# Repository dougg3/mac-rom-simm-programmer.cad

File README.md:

# Mac ROM SIMM and Programmer PCBs

These are the CAD files for the Mac ROM SIMM and programmer project.

- 2mbsimm/ contains a FreePCB board layout file for the 2 MB ROM SIMM.
- 2mbsimm-dip/ contains Eagle schematics and board layout files for the 2 MB ROM SIMM for DIP chips.
- 8mbsimm/ contains Eagle schematics and board layout files for the 8 MB ROM SIMM.
- programmer/ contains Eagle schematics and board layout files for the SIMM programmer.

See [LICENSE.txt](https://github.com/dougg3/mac-rom-simm-programmer.cad/blob/master/LICENSE.txt) for information on the license of these PCBs. They are licensed under the [Creative Commons Attribution-NonCommercial 3.0 license](https://creativecommons.org/licenses/by-nc/3.0/legalcode). Feel free to make your own SIMMs and/or programmers for personal use, but do not sell them commercially.

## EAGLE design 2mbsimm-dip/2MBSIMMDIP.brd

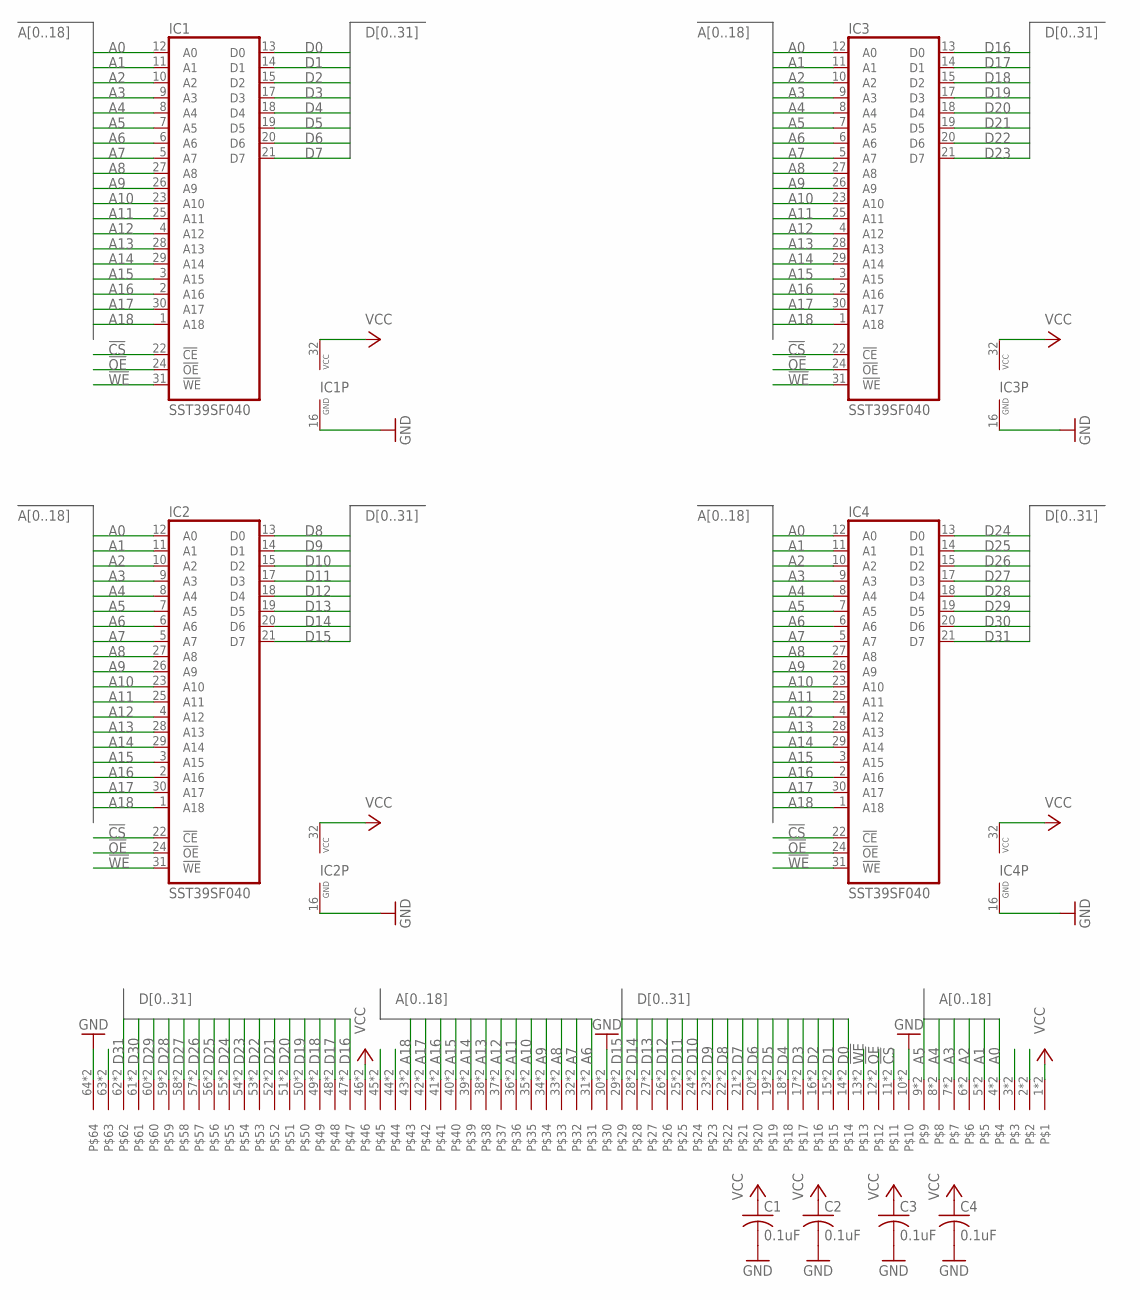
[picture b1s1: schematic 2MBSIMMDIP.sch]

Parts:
C1, C2, C3, C4: 0.1uF; C1206
CON1: MYSIMM; SIMM64L
IC1, IC2, IC3, IC4: SST39SF040; DIL32-6

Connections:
!CS: CON1.11, CON1.75, IC1.22 (!CE), IC2.22 (!CE), IC3.22 (!CE), IC4.22 (!CE)
!OE: CON1.12, CON1.76, IC1.24 (!OE), IC2.24 (!OE), IC3.24 (!OE), IC4.24 (!OE)
!WE: CON1.13, CON1.77, IC1.31 (!WE), IC2.31 (!WE), IC3.31 (!WE), IC4.31 (!WE)
A0: CON1.4, CON1.68, IC1.12 (A0), IC2.12 (A0), IC3.12 (A0), IC4.12 (A0)
A1: CON1.5, CON1.69, IC1.11 (A1), IC2.11 (A1), IC3.11 (A1), IC4.11 (A1)
A2: CON1.6, CON1.70, IC1.10 (A2), IC2.10 (A2), IC3.10 (A2), IC4.10 (A2)
A3: CON1.7, CON1.71, IC1.9 (A3), IC2.9 (A3), IC3.9 (A3), IC4.9 (A3)
A4: CON1.8, CON1.72, IC1.8 (A4), IC2.8 (A4), IC3.8 (A4), IC4.8 (A4)
A5: CON1.9, CON1.73, IC1.7 (A5), IC2.7 (A5), IC3.7 (A5), IC4.7 (A5)
A6: CON1.31, CON1.95, IC1.6 (A6), IC2.6 (A6), IC3.6 (A6), IC4.6 (A6)
A7: CON1.32, CON1.96, IC1.5 (A7), IC2.5 (A7), IC3.5 (A7), IC4.5 (A7)
A8: CON1.33, CON1.97, IC1.27 (A8), IC2.27 (A8), IC3.27 (A8), IC4.27 (A8)
A9: CON1.34, CON1.98, IC1.26 (A9), IC2.26 (A9), IC3.26 (A9), IC4.26 (A9)
A10: CON1.35, CON1.99, IC1.23 (A10), IC2.23 (A10), IC3.23 (A10), IC4.23 (A10)
A11: CON1.36, CON1.100, IC1.25 (A11), IC2.25 (A11), IC3.25 (A11), IC4.25 (A11)
A12: CON1.37, CON1.101, IC1.4 (A12), IC2.4 (A12), IC3.4 (A12), IC4.4 (A12)
A13: CON1.38, CON1.102, IC1.28 (A13), IC2.28 (A13), IC3.28 (A13), IC4.28 (A13)
A14: CON1.39, CON1.103, IC1.29 (A14), IC2.29 (A14), IC3.29 (A14), IC4.29 (A14)
A15: CON1.40, CON1.104, IC1.3 (A15), IC2.3 (A15), IC3.3 (A15), IC4.3 (A15)
A16: CON1.41, CON1.105, IC1.2 (A16), IC2.2 (A16), IC3.2 (A16), IC4.2 (A16)
A17: CON1.42, CON1.106, IC1.30 (A17), IC2.30 (A17), IC3.30 (A17), IC4.30 (A17)
A18: CON1.43, CON1.107, IC1.1 (A18), IC2.1 (A18), IC3.1 (A18), IC4.1 (A18)
D0: CON1.14, CON1.78, IC1.13 (D0)
D1: CON1.15, CON1.79, IC1.14 (D1)
D2: CON1.16, CON1.80, IC1.15 (D2)
D3: CON1.17, CON1.81, IC1.17 (D3)
D4: CON1.18, CON1.82, IC1.18 (D4)
D5: CON1.19, CON1.83, IC1.19 (D5)
D6: CON1.20, CON1.84, IC1.20 (D6)
D7: CON1.21, CON1.85, IC1.21 (D7)
D8: CON1.22, CON1.86, IC2.13 (D0)
D9: CON1.23, CON1.87, IC2.14 (D1)
D10: CON1.24, CON1.88, IC2.15 (D2)
D11: CON1.25, CON1.89, IC2.17 (D3)
D12: CON1.26, CON1.90, IC2.18 (D4)
D13: CON1.27, CON1.91, IC2.19 (D5)
D14: CON1.28, CON1.92, IC2.20 (D6)
D15: CON1.29, CON1.93, IC2.21 (D7)
D16: CON1.47, CON1.111, IC3.13 (D0)
D17: CON1.48, CON1.112, IC3.14 (D1)
D18: CON1.49, CON1.113, IC3.15 (D2)
D19: CON1.50, CON1.114, IC3.17 (D3)
D20: CON1.51, CON1.115, IC3.18 (D4)
D21: CON1.52, CON1.116, IC3.19 (D5)
D22: CON1.53, CON1.117, IC3.20 (D6)
D23: CON1.54, CON1.118, IC3.21 (D7)
D24: CON1.55, CON1.119, IC4.13 (D0)
D25: CON1.56, CON1.120, IC4.14 (D1)
D26: CON1.57, CON1.121, IC4.15 (D2)
D27: CON1.58, CON1.122, IC4.17 (D3)
D28: CON1.59, CON1.123, IC4.18 (D4)
D29: CON1.60, CON1.124, IC4.19 (D5)
D30: CON1.61, CON1.125, IC4.20 (D6)
D31: CON1.62, CON1.126, IC4.21 (D7)
GND: C1.2, C2.2, C3.2, C4.2, CON1.10, CON1.30, CON1.64, CON1.74, CON1.94, CON1.128, IC1.16 (GND), IC2.16 (GND), IC3.16 (GND), IC4.16 (GND)
UNUSED1: CON1.2, CON1.66
UNUSED2: CON1.3, CON1.67
UNUSED3: CON1.63, CON1.127
UNUSED4: CON1.44, CON1.108
UNUSED5: CON1.45, CON1.109
VCC: C1.1, C2.1, C3.1, C4.1, CON1.1, CON1.46, CON1.65, CON1.110, IC1.32 (VCC), IC2.32 (VCC), IC3.32 (VCC), IC4.32 (VCC)

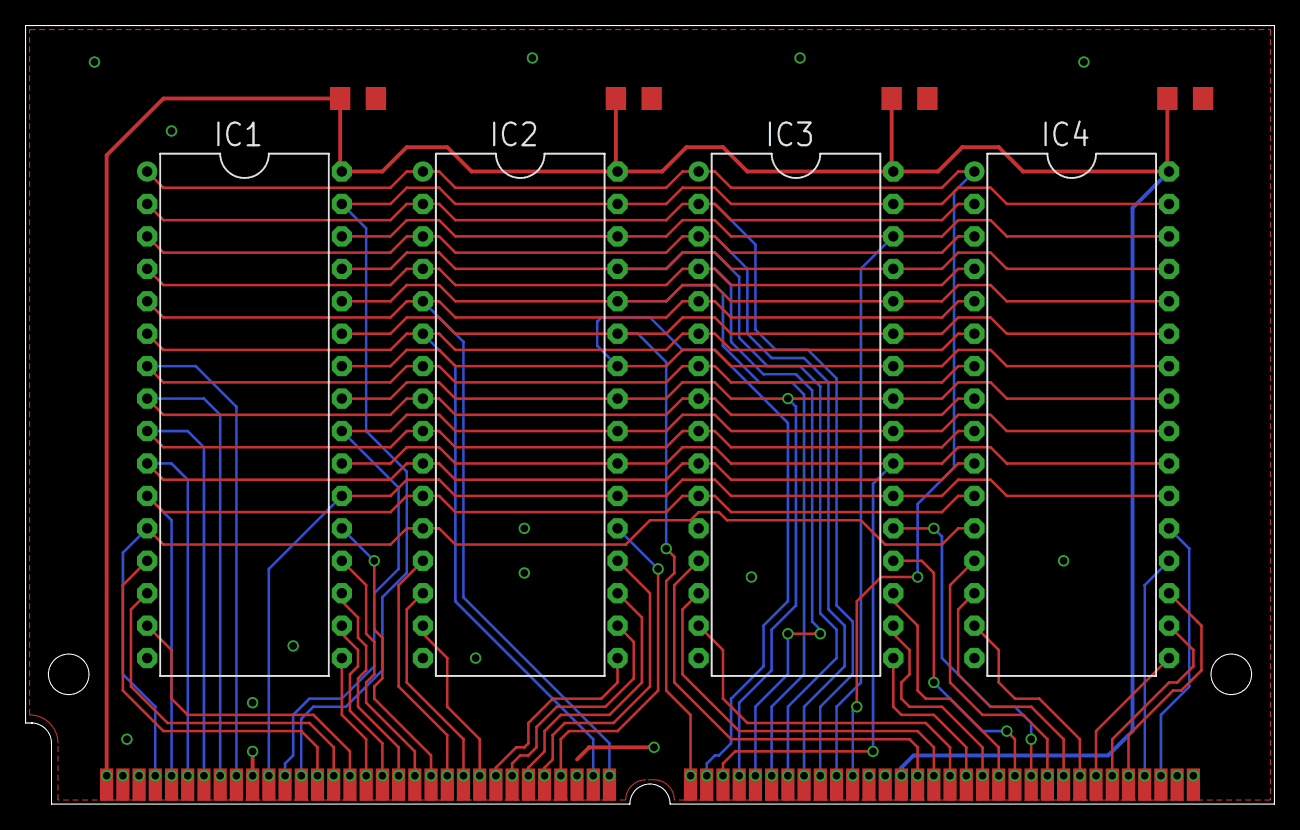
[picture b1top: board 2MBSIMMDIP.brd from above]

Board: 2 copper layers, 97.8 x 61.0 mm, 9 parts (0 on the bottom side), 61 nets.

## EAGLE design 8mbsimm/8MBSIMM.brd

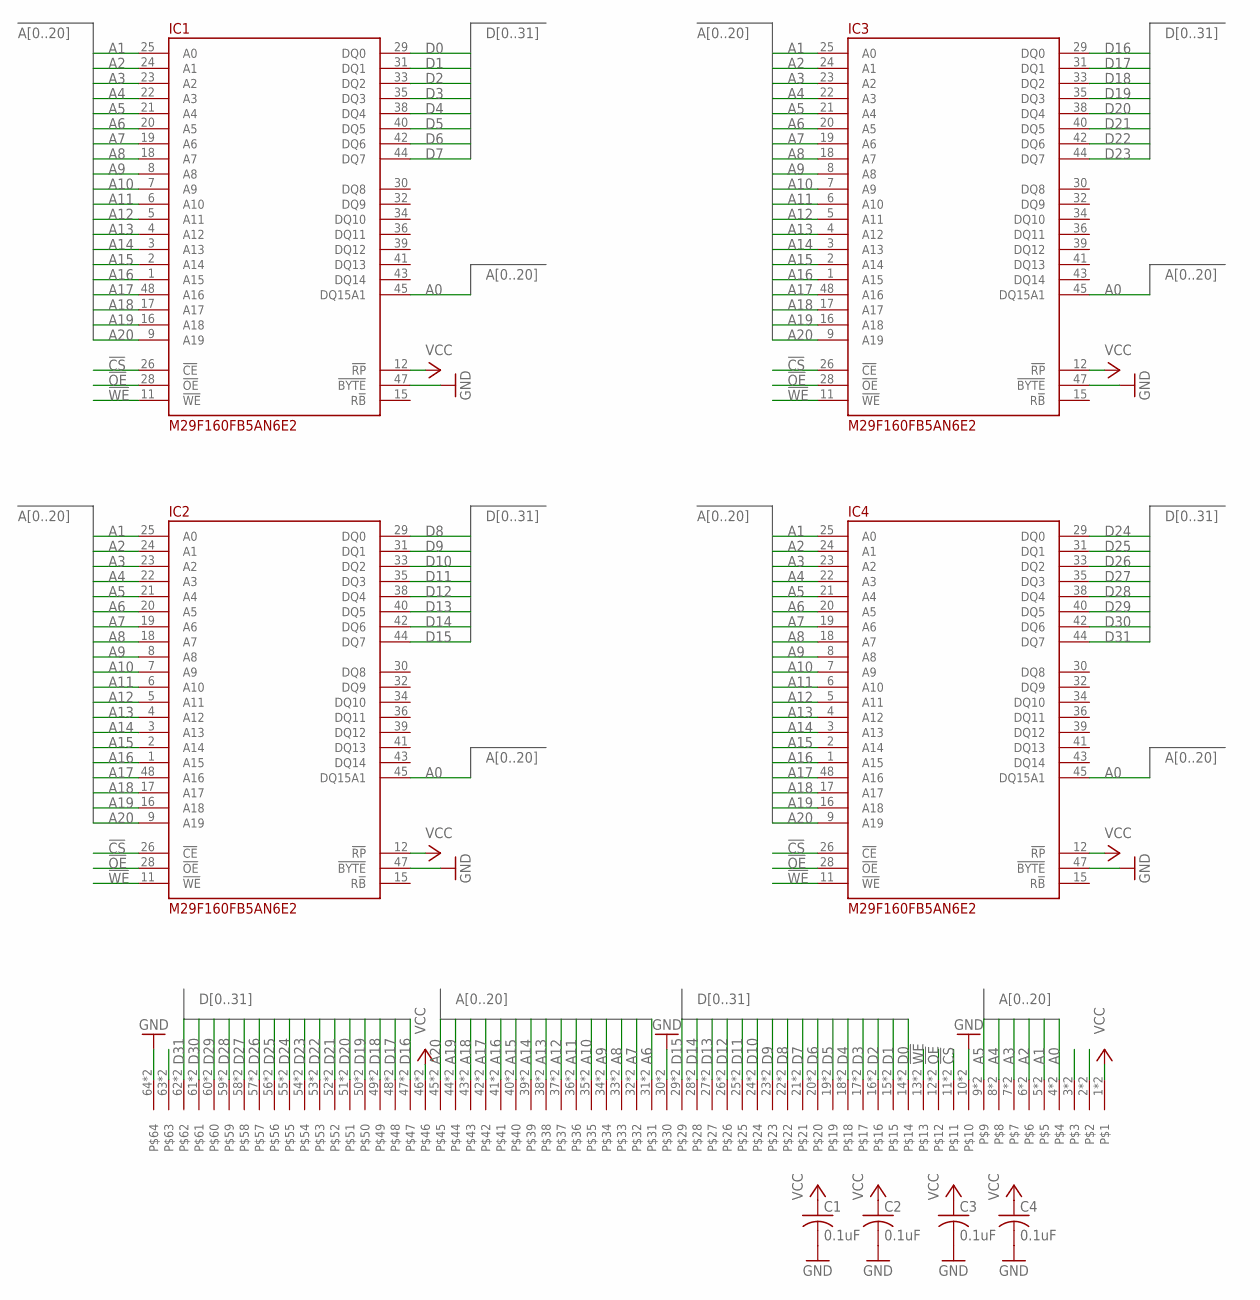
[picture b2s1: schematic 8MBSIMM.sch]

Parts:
C1, C2, C3, C4: 0.1uF; C1206
CON1: MYSIMM; SIMM64L
IC1, IC2, IC3, IC4: M29F160FB5AN6E2; TSOP48

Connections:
!CS: CON1.11, CON1.75, IC1.26 (!CE), IC2.26 (!CE), IC3.26 (!CE), IC4.26 (!CE)
!OE: CON1.12, CON1.76, IC1.28 (!OE), IC2.28 (!OE), IC3.28 (!OE), IC4.28 (!OE)
!WE: CON1.13, CON1.77, IC1.11 (!WE), IC2.11 (!WE), IC3.11 (!WE), IC4.11 (!WE)
A0: CON1.4, CON1.68, IC1.45 (DQ15A1), IC2.45 (DQ15A1), IC3.45 (DQ15A1), IC4.45 (DQ15A1)
A1: CON1.5, CON1.69, IC1.25 (A0), IC2.25 (A0), IC3.25 (A0), IC4.25 (A0)
A2: CON1.6, CON1.70, IC1.24 (A1), IC2.24 (A1), IC3.24 (A1), IC4.24 (A1)
A3: CON1.7, CON1.71, IC1.23 (A2), IC2.23 (A2), IC3.23 (A2), IC4.23 (A2)
A4: CON1.8, CON1.72, IC1.22 (A3), IC2.22 (A3), IC3.22 (A3), IC4.22 (A3)
A5: CON1.9, CON1.73, IC1.21 (A4), IC2.21 (A4), IC3.21 (A4), IC4.21 (A4)
A6: CON1.31, CON1.95, IC1.20 (A5), IC2.20 (A5), IC3.20 (A5), IC4.20 (A5)
A7: CON1.32, CON1.96, IC1.19 (A6), IC2.19 (A6), IC3.19 (A6), IC4.19 (A6)
A8: CON1.33, CON1.97, IC1.18 (A7), IC2.18 (A7), IC3.18 (A7), IC4.18 (A7)
A9: CON1.34, CON1.98, IC1.8 (A8), IC2.8 (A8), IC3.8 (A8), IC4.8 (A8)
A10: CON1.35, CON1.99, IC1.7 (A9), IC2.7 (A9), IC3.7 (A9), IC4.7 (A9)
A11: CON1.36, CON1.100, IC1.6 (A10), IC2.6 (A10), IC3.6 (A10), IC4.6 (A10)
A12: CON1.37, CON1.101, IC1.5 (A11), IC2.5 (A11), IC3.5 (A11), IC4.5 (A11)
A13: CON1.38, CON1.102, IC1.4 (A12), IC2.4 (A12), IC3.4 (A12), IC4.4 (A12)
A14: CON1.39, CON1.103, IC1.3 (A13), IC2.3 (A13), IC3.3 (A13), IC4.3 (A13)
A15: CON1.40, CON1.104, IC1.2 (A14), IC2.2 (A14), IC3.2 (A14), IC4.2 (A14)
A16: CON1.41, CON1.105, IC1.1 (A15), IC2.1 (A15), IC3.1 (A15), IC4.1 (A15)
A17: CON1.42, CON1.106, IC1.48 (A16), IC2.48 (A16), IC3.48 (A16), IC4.48 (A16)
A18: CON1.43, CON1.107, IC1.17 (A17), IC2.17 (A17), IC3.17 (A17), IC4.17 (A17)
A19: CON1.44, CON1.108, IC1.16 (A18), IC2.16 (A18), IC3.16 (A18), IC4.16 (A18)
A20: CON1.45, CON1.109, IC1.9 (A19), IC2.9 (A19), IC3.9 (A19), IC4.9 (A19)
D0: CON1.14, CON1.78, IC1.29 (DQ0)
D1: CON1.15, CON1.79, IC1.31 (DQ1)
D2: CON1.16, CON1.80, IC1.33 (DQ2)
D3: CON1.17, CON1.81, IC1.35 (DQ3)
D4: CON1.18, CON1.82, IC1.38 (DQ4)
D5: CON1.19, CON1.83, IC1.40 (DQ5)
D6: CON1.20, CON1.84, IC1.42 (DQ6)
D7: CON1.21, CON1.85, IC1.44 (DQ7)
D8: CON1.22, CON1.86, IC2.29 (DQ0)
D9: CON1.23, CON1.87, IC2.31 (DQ1)
D10: CON1.24, CON1.88, IC2.33 (DQ2)
D11: CON1.25, CON1.89, IC2.35 (DQ3)
D12: CON1.26, CON1.90, IC2.38 (DQ4)
D13: CON1.27, CON1.91, IC2.40 (DQ5)
D14: CON1.28, CON1.92, IC2.42 (DQ6)
D15: CON1.29, CON1.93, IC2.44 (DQ7)
D16: CON1.47, CON1.111, IC3.29 (DQ0)
D17: CON1.48, CON1.112, IC3.31 (DQ1)
D18: CON1.49, CON1.113, IC3.33 (DQ2)
D19: CON1.50, CON1.114, IC3.35 (DQ3)
D20: CON1.51, CON1.115, IC3.38 (DQ4)
D21: CON1.52, CON1.116, IC3.40 (DQ5)
D22: CON1.53, CON1.117, IC3.42 (DQ6)
D23: CON1.54, CON1.118, IC3.44 (DQ7)
D24: CON1.55, CON1.119, IC4.29 (DQ0)
D25: CON1.56, CON1.120, IC4.31 (DQ1)
D26: CON1.57, CON1.121, IC4.33 (DQ2)
D27: CON1.58, CON1.122, IC4.35 (DQ3)
D28: CON1.59, CON1.123, IC4.38 (DQ4)
D29: CON1.60, CON1.124, IC4.40 (DQ5)
D30: CON1.61, CON1.125, IC4.42 (DQ6)
D31: CON1.62, CON1.126, IC4.44 (DQ7)
GND: C1.2, C2.2, C3.2, C4.2, CON1.10, CON1.30, CON1.64, CON1.74, CON1.94, CON1.128, IC1.27 (GND), IC1.46 (GND), IC1.47 (!BYTE), IC2.27 (GND), IC2.46 (GND), IC2.47 (!BYTE), IC3.27 (GND), IC3.46 (GND), IC3.47 (!BYTE), IC4.27 (GND), IC4.46 (GND), IC4.47 (!BYTE)
UNUSED1: CON1.2, CON1.66
UNUSED2: CON1.3, CON1.67
UNUSED3: CON1.63, CON1.127
VCC: C1.1, C2.1, C3.1, C4.1, CON1.1, CON1.46, CON1.65, CON1.110, IC1.12 (!RP), IC1.37 (VCC), IC2.12 (!RP), IC2.37 (VCC), IC3.12 (!RP), IC3.37 (VCC), IC4.12 (!RP), IC4.37 (VCC)

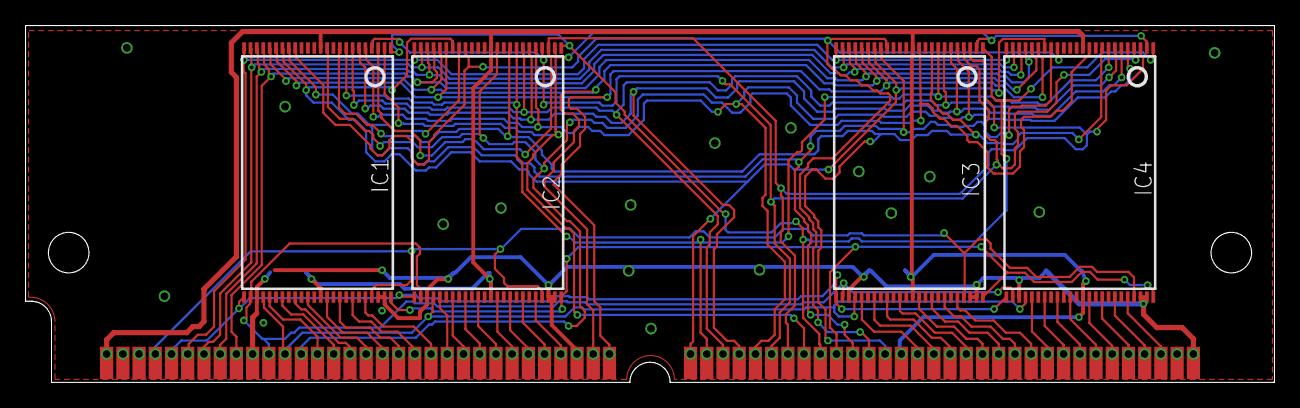
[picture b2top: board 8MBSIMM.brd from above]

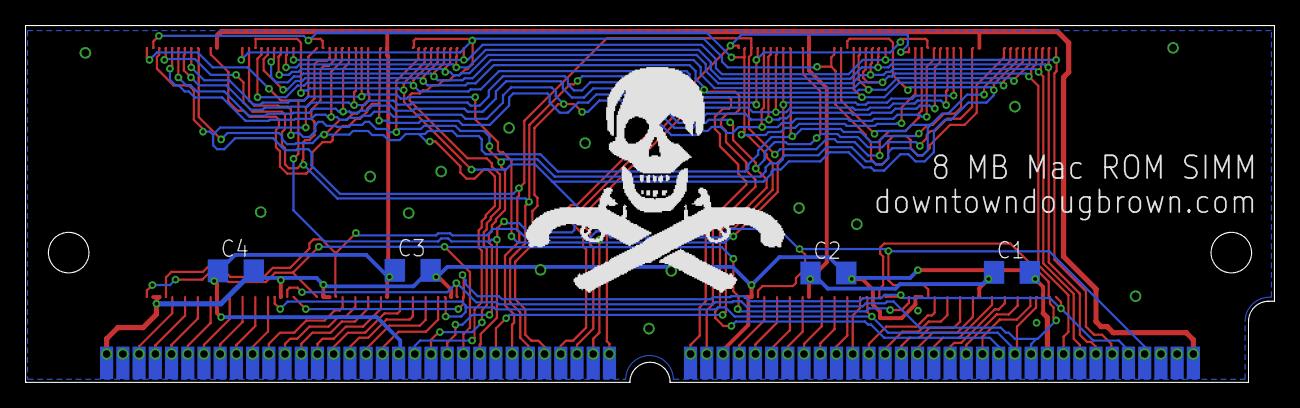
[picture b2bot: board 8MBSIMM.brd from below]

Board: 4 copper layers, 97.8 x 27.9 mm, 10 parts (5 on the bottom side), 61 nets.

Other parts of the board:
U$1: JOLLYROGER

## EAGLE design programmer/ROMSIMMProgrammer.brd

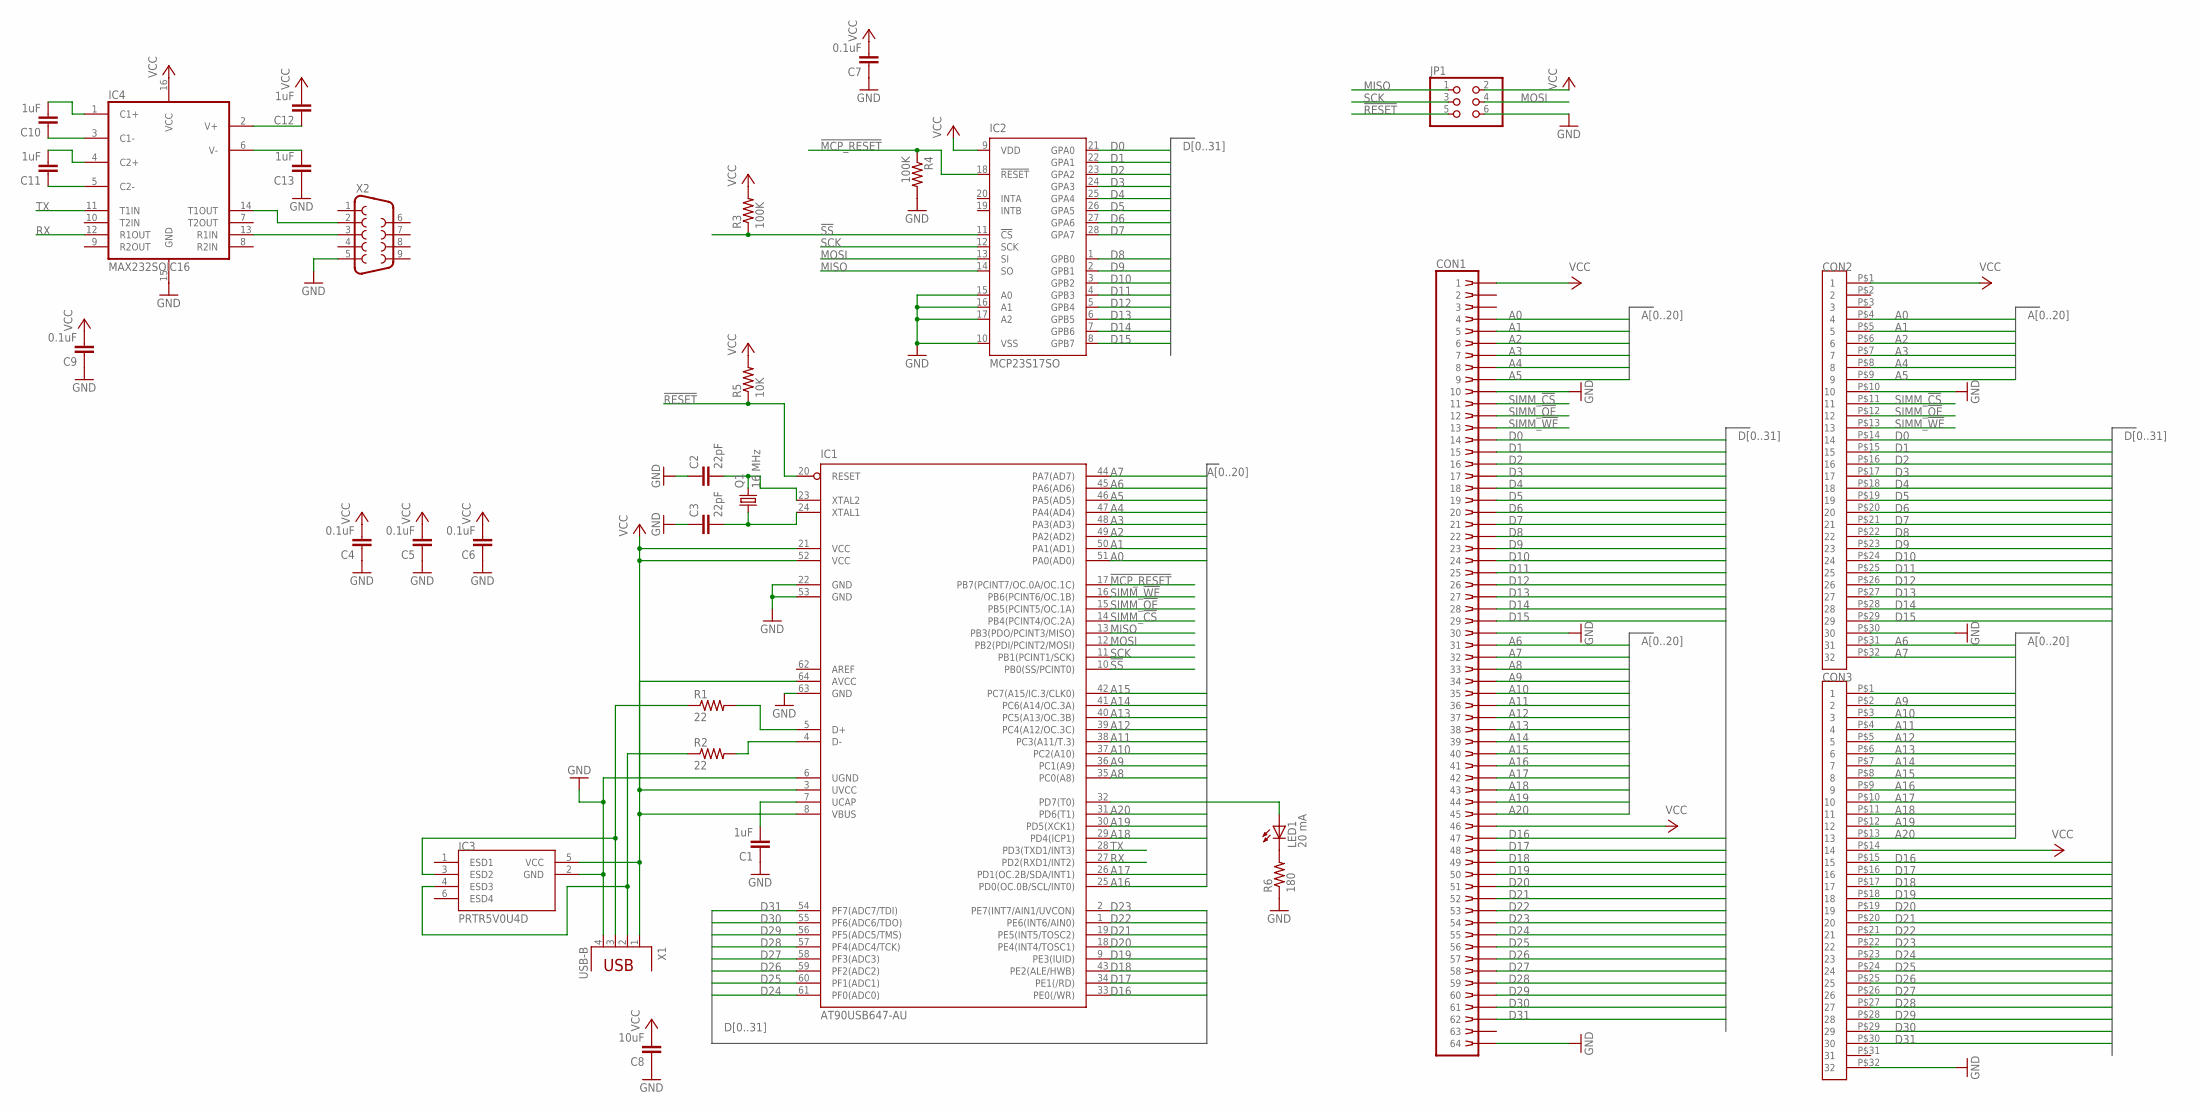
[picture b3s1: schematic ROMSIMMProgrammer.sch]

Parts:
C1, C10, C11, C12, C13: 1uF; C0805
C2, C3: 22pF; C0805
C4, C5, C6, C7, C9: 0.1uF; C0805
C8: 10uF; C0805
CON1: SIMM64; 822032-2
CON2, CON3: SMS-132-01-G-S
IC1: AT90USB647-AU; TQFP64
IC2: MCP23S17SO; SO28W
IC3: PRTR5V0U4D; SOT457R_PHILIPS
IC4: MAX232SOIC16; SO016
JP1: PINHD-2X3; 2X03
LED1: 20 mA; CHIP-LED0805
Q1: 16 MHz; HC49UP
R1, R2: 22; R0805
R3, R4: 100K; R0805
R5: 10K; R0805
R6: 180; R0805
X1: USB-B; PN61729
X2: DB9FEMALE; DB9

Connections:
!MCP_RESET: IC1.17 (PB7(PCINT7/OC.0A/OC.1C)), IC2.18 (!RESET), R4.1
!RESET: IC1.20 (RESET), JP1.5, R5.1
!SS: IC1.10 (PB0(SS/PCINT0)), IC2.11 (!CS), R3.1
A0: CON1.4, CON2.P$4 (4), IC1.51 (PA0(AD0))
A1: CON1.5, CON2.P$5 (5), IC1.50 (PA1(AD1))
A2: CON1.6, CON2.P$6 (6), IC1.49 (PA2(AD2))
A3: CON1.7, CON2.P$7 (7), IC1.48 (PA3(AD3))
A4: CON1.8, CON2.P$8 (8), IC1.47 (PA4(AD4))
A5: CON1.9, CON2.P$9 (9), IC1.46 (PA5(AD5))
A6: CON1.31, CON2.P$31 (31), IC1.45 (PA6(AD6))
A7: CON1.32, CON2.P$32 (32), IC1.44 (PA7(AD7))
A8: CON1.33, CON3.P$1 (1), IC1.35 (PC0(A8))
A9: CON1.34, CON3.P$2 (2), IC1.36 (PC1(A9))
A10: CON1.35, CON3.P$3 (3), IC1.37 (PC2(A10))
A11: CON1.36, CON3.P$4 (4), IC1.38 (PC3(A11/T.3))
A12: CON1.37, CON3.P$5 (5), IC1.39 (PC4(A12/OC.3C))
A13: CON1.38, CON3.P$6 (6), IC1.40 (PC5(A13/OC.3B))
A14: CON1.39, CON3.P$7 (7), IC1.41 (PC6(A14/OC.3A))
A15: CON1.40, CON3.P$8 (8), IC1.42 (PC7(A15/IC.3/CLK0))
A16: CON1.41, CON3.P$9 (9), IC1.25 (PD0(OC.0B/SCL/INT0))
A17: CON1.42, CON3.P$10 (10), IC1.26 (PD1(OC.2B/SDA/INT1))
A18: CON1.43, CON3.P$11 (11), IC1.29 (PD4(ICP1))
A19: CON1.44, CON3.P$12 (12), IC1.30 (PD5(XCK1))
A20: CON1.45, CON3.P$13 (13), IC1.31 (PD6(T1))
D0: CON1.14, CON2.P$14 (14), IC2.21 (GPA0)
D1: CON1.15, CON2.P$15 (15), IC2.22 (GPA1)
D2: CON1.16, CON2.P$16 (16), IC2.23 (GPA2)
D3: CON1.17, CON2.P$17 (17), IC2.24 (GPA3)
D4: CON1.18, CON2.P$18 (18), IC2.25 (GPA4)
D5: CON1.19, CON2.P$19 (19), IC2.26 (GPA5)
D6: CON1.20, CON2.P$20 (20), IC2.27 (GPA6)
D7: CON1.21, CON2.P$21 (21), IC2.28 (GPA7)
D8: CON1.22, CON2.P$22 (22), IC2.1 (GPB0)
D9: CON1.23, CON2.P$23 (23), IC2.2 (GPB1)
D10: CON1.24, CON2.P$24 (24), IC2.3 (GPB2)
D11: CON1.25, CON2.P$25 (25), IC2.4 (GPB3)
D12: CON1.26, CON2.P$26 (26), IC2.5 (GPB4)
D13: CON1.27, CON2.P$27 (27), IC2.6 (GPB5)
D14: CON1.28, CON2.P$28 (28), IC2.7 (GPB6)
D15: CON1.29, CON2.P$29 (29), IC2.8 (GPB7)
D16: CON1.47, CON3.P$15 (15), IC1.33 (PE0(/WR))
D17: CON1.48, CON3.P$16 (16), IC1.34 (PE1(/RD))
D18: CON1.49, CON3.P$17 (17), IC1.43 (PE2(ALE/HWB))
D19: CON1.50, CON3.P$18 (18), IC1.9 (PE3(IUID))
D20: CON1.51, CON3.P$19 (19), IC1.18 (PE4(INT4/TOSC1))
D21: CON1.52, CON3.P$20 (20), IC1.19 (PE5(INT5/TOSC2))
D22: CON1.53, CON3.P$21 (21), IC1.1 (PE6(INT6/AIN0))
D23: CON1.54, CON3.P$22 (22), IC1.2 (PE7(INT7/AIN1/UVCON))
D24: CON1.55, CON3.P$23 (23), IC1.61 (PF0(ADC0))
D25: CON1.56, CON3.P$24 (24), IC1.60 (PF1(ADC1))
D26: CON1.57, CON3.P$25 (25), IC1.59 (PF2(ADC2))
D27: CON1.58, CON3.P$26 (26), IC1.58 (PF3(ADC3))
D28: CON1.59, CON3.P$27 (27), IC1.57 (PF4(ADC4/TCK))
D29: CON1.60, CON3.P$28 (28), IC1.56 (PF5(ADC5/TMS))
D30: CON1.61, CON3.P$29 (29), IC1.55 (PF6(ADC6/TDO))
D31: CON1.62, CON3.P$30 (30), IC1.54 (PF7(ADC7/TDI))
D+: IC3.3 (ESD2), R1.1, X1.3
D-: IC3.4 (ESD3), R2.1, X1.2
GND: C1.1, C2.1, C3.1, C4.1, C5.1, C6.1, C7.1, C8.1, C9.1, C13.1, CON1.10, CON1.30, CON1.64, CON2.P$10 (10), CON2.P$30 (30), CON3.P$32 (32), IC1.6 (UGND), IC1.22 (GND), IC1.53 (GND), IC1.63 (GND), IC2.10 (VSS), IC2.15 (A0), IC2.16 (A1), IC2.17 (A2), IC3.2 (GND), IC4.15 (GND), JP1.6, R4.2, R6.1, X1.4, X2.5
MISO: IC1.13 (PB3(PDO/PCINT3/MISO)), IC2.14 (SO), JP1.1
MOSI: IC1.12 (PB2(PDI/PCINT2/MOSI)), IC2.13 (SI), JP1.4
unnamed: IC1.5 (D+), R1.2
unnamed: IC1.4 (D-), R2.2
unnamed: C2.2, IC1.23 (XTAL2), Q1.2
unnamed: C3.2, IC1.24 (XTAL1), Q1.1
unnamed: C10.2, IC4.1 (C1+)
unnamed: C1.2, IC1.7 (UCAP)
unnamed: C10.1, IC4.3 (C1-)
unnamed: C11.1, IC4.5 (C2-)
unnamed: C11.2, IC4.4 (C2+)
unnamed: C12.1, IC4.2 (V+)
unnamed: C13.2, IC4.6 (V-)
unnamed: IC4.14 (T1OUT), X2.2
unnamed: IC4.13 (R1IN), X2.3
unnamed: IC1.32 (PD7(T0)), LED1.A
unnamed: LED1.C, R6.2
RX: IC1.27 (PD2(RXD1/INT2)), IC4.12 (R1OUT)
SCK: IC1.11 (PB1(PCINT1/SCK)), IC2.12 (SCK), JP1.3
SIMM_!CS: CON1.11, CON2.P$11 (11), IC1.14 (PB4(PCINT4/OC.2A))
SIMM_!OE: CON1.12, CON2.P$12 (12), IC1.15 (PB5(PCINT5/OC.1A))
SIMM_!WE: CON1.13, CON2.P$13 (13), IC1.16 (PB6(PCINT6/OC.1B))
TX: IC1.28 (PD3(TXD1/INT3)), IC4.11 (T1IN)
VCC: C4.2, C5.2, C6.2, C7.2, C8.2, C9.2, C12.2, CON1.1, CON1.46, CON2.P$1 (1), CON3.P$14 (14), IC1.3 (UVCC), IC1.8 (VBUS), IC1.21 (VCC), IC1.52 (VCC), IC1.64 (AVCC), IC2.9 (VDD), IC3.5 (VCC), IC4.16 (VCC), JP1.2, R3.2, R5.2, X1.1

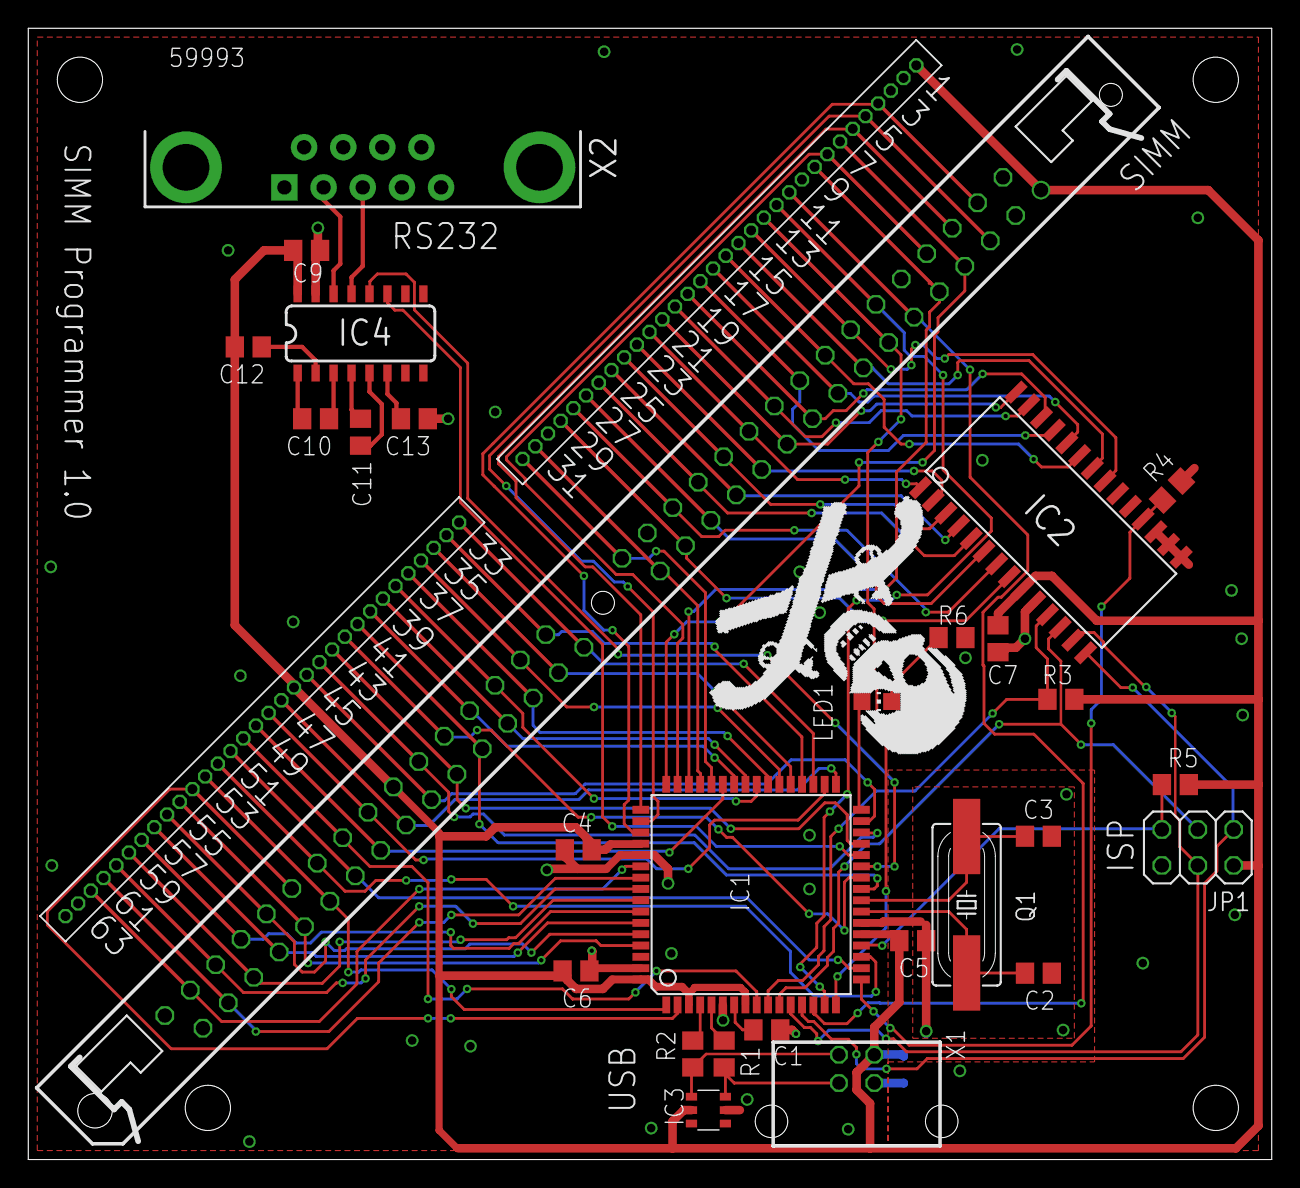
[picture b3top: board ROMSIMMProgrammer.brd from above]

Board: 2 copper layers, 87.9 x 80.0 mm, 32 parts (1 on the bottom side), 83 nets.

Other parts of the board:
U$1: JOLLYROGER

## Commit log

2012-10-01 Initial import of CAD files into repository.
    2mbsimm/ contains the 2 MB SIMM, revision 3 (FreePCB)
    8mbsimm/ contains the 8 MB SIMM, revision 1 (Eagle)
    programmer/ contains the programmer, revision 1.0 (Eagle)
2012-10-21 Changed for final revision: moved jolly roger logo to center.
2014-03-02 Added label and URL to silkscreen, ran against latest design rules.
2014-03-07 Adding license file.
2015-01-01 Added 2 MB SIMM with DIP sockets
2020-11-29 Update README
    Make it markdown instead, format it nicely, add info about license to make it clear
